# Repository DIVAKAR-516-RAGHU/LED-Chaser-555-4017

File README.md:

# 10-Stage Sequential LED Chaser (NE555 + CD4017)

A fully verified, 2-layer hardware design of a 10-stage sequential LED chaser circuit designed in **KiCad**. The board incorporates an analog astable pulse generator driving a CMOS Johnson decade counter with dedicated current-limited output stages and integrated ground copper fills.

---

## ⚡ Circuit Overview & Working Principle

The circuit is organized into three sequential functional stages:

1. **Clock Generator (NE555 Timer - Astable Mode):**
   * Configured as an astable multivibrator producing continuous square-wave clock pulses.
   * Timing is governed by external resistors $R_1$, $R_2$ and timing capacitor $C_1$:
     $$f \approx \frac{1.44}{(R_1 + 2R_2) \cdot C_1}$$
   * The output from pin 3 feeds directly into the clock input of the counter.

2. **Decade Counter & Sequencer (CD4017):**
   * High-speed CMOS 5-stage Johnson decade counter with 10 decoded active-high outputs ($Q_0$ through $Q_9$).
   * Advances one count on every positive clock edge received from the 555 timer.
   * Clock Inhibit (pin 13) and Master Reset (pin 15) are tied to ground for continuous, rollover cycling.

3. **Output Display (LED Array):**
   * 10 sequential 5 mm LEDs ($D_1$ to $D_{10}$), each paired with an independent 1 kΩ current-limiting resistor ($R_3$ to $R_{12}$) to maintain uniform brightness and prevent current crowding.

---

## 🛠️ Hardware & PCB Specifications

* **EDA Tool:** KiCad 8.0+
* **Layer Count:** 2-Layer (Top Copper / Bottom Copper)
* **Board Dimensions:** Defined via enclosed `Edge.Cuts` boundary
* **Substrate / Thickness:** FR-4 / 1.6 mm
* **Copper Weight:** 1 oz (35 µm)
* **Minimum Trace Width:** 0.25 mm (Signals) / 0.5 mm (Power rails)
* **Ground Strategy:** Solid ground fill on bottom copper (`B.Cu`) with thermal relief spokes on all grounded through-hole pads.
* **Decoupling / EMI Protection:** Dedicated 100 nF ceramic bypass capacitors located directly adjacent to $V_{CC}$ and $V_{DD}$ supply pins to suppress switching transients.
* **Design Verification:** Passed with **0 ERC (Electrical Rules Check)** and **0 DRC (Design Rules Check)** errors.

---

## 📋 Bill of Materials (BOM)

| Designator | Description / Value | Package / Footprint | Quantity |
| :--- | :--- | :--- | :--- |
| **U1** | NE555 Precision Timer IC | DIP-8 | 1 |
| **U2** | CD4017 Decade Counter/Divider IC | DIP-16 | 1 |
| **D1 – D10** | 5 mm Through-Hole LEDs | Radial LED 5 mm | 10 |
| **R1** | 10 kΩ Resistor, 1/4W | Axial Through-Hole | 1 |
| **R2** | 100 kΩ Resistor, 1/4W | Axial Through-Hole | 1 |
| **R3 – R12** | 1 kΩ Resistors, 1/4W | Axial Through-Hole | 10 |
| **C1** | 10 µF Electrolytic Capacitor | Radial 2.54 mm pitch | 1 |
| **C2** | 10 nF Ceramic Disc Capacitor | Radial 2.54 mm pitch | 1 |
| **C3, C4** | 100 nF Ceramic Bypass Capacitors | Radial 2.54 mm pitch | 2 |
| **J1** | 2-Pin Screw Terminal or 2.54 mm Header | 1x02 2.54 mm Pitch | 1 |

---

## 📁 Repository Structure

```text
├── Hardware/                         # Native KiCad design files
│   ├── LED Chaser (CD4017 + 555).kicad_pro
│   ├── LED Chaser (CD4017 + 555).kicad_sch
│   └── LED Chaser (CD4017 + 555).kicad_pcb
├── Production/                       # Manufacturing outputs
│   └── LED_Chaser_Fabrication.zip   # Gerber & Excellon drill files
├── assets/                           # Media & layout previews
│   ├── 3d_render.png
│   ├── pcb_layout.png
│   └── schematic_preview.png
├── .gitignore
└── README.md

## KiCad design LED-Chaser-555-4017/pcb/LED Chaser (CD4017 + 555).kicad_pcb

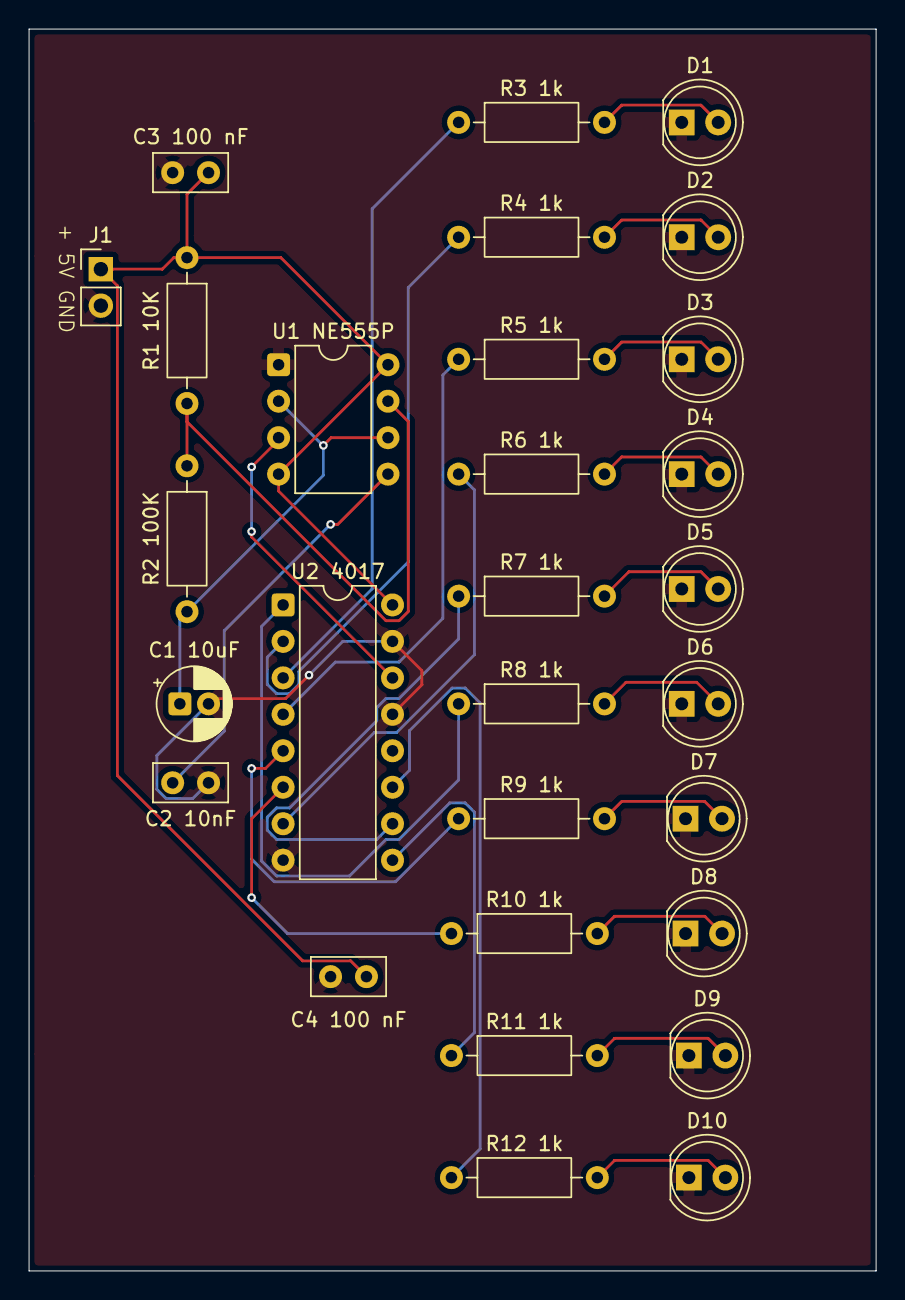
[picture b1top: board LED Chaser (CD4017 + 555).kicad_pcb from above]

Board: 2 copper layers, 59.0 x 86.5 mm, 29 parts (0 on the bottom side), 26 nets.

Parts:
C1 10uF: 10 uF; CP_Radial_D5.0mm_P2.00mm
C2 10nF: 10 nF; C_Disc_D5.0mm_W2.5mm_P2.50mm
C3 100 nF, C4 100 nF: 100 nF; C_Disc_D5.0mm_W2.5mm_P2.50mm
D1: D1 LED; LED_D5.0mm
D2: D2 LED; LED_D5.0mm
D3: D3 LED; LED_D5.0mm
D4: D4 LED; LED_D5.0mm
D5: D5 LED; LED_D5.0mm
D6: D6 LED; LED_D5.0mm
D7: D7 LED; LED_D5.0mm
D8: D8 LED; LED_D5.0mm
D9: D9 LED; LED_D5.0mm
D10: D10 LED; LED_D5.0mm
J1: Conn_01x02; PinHeader_1x02_P2.54mm_Vertical
R1 10K: 10k; R_Axial_DIN0207_L6.3mm_D2.5mm_P10.16mm_Horizontal
R2 100K: 100k; R_Axial_DIN0207_L6.3mm_D2.5mm_P10.16mm_Horizontal
R3 1k: R3 1k; R_Axial_DIN0207_L6.3mm_D2.5mm_P10.16mm_Horizontal
R4 1k: R4 1k; R_Axial_DIN0207_L6.3mm_D2.5mm_P10.16mm_Horizontal
R5 1k: R5 1k; R_Axial_DIN0207_L6.3mm_D2.5mm_P10.16mm_Horizontal
R6 1k: R6 1k; R_Axial_DIN0207_L6.3mm_D2.5mm_P10.16mm_Horizontal
R7 1k: R7 1k; R_Axial_DIN0207_L6.3mm_D2.5mm_P10.16mm_Horizontal
R8 1k: R8 1k; R_Axial_DIN0207_L6.3mm_D2.5mm_P10.16mm_Horizontal
R9 1k: R9 1k; R_Axial_DIN0207_L6.3mm_D2.5mm_P10.16mm_Horizontal
R10 1k: R10 1k; R_Axial_DIN0207_L6.3mm_D2.5mm_P10.16mm_Horizontal
R11 1k: R11 1k; R_Axial_DIN0207_L6.3mm_D2.5mm_P10.16mm_Horizontal
R12 1k: R12 1k; R_Axial_DIN0207_L6.3mm_D2.5mm_P10.16mm_Horizontal
U1 NE555P: NE555P; DIP-8_W7.62mm
U2 4017: 4017; DIP-16_W7.62mm

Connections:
+5V: C3 100 nF.2, C4 100 nF.2, J1.1, R1 10K.1, U1 NE555P.4 (~RST), U1 NE555P.8 (VCC), U2 4017.16 (VDD)
/CLOCK: U1 NE555P.3 (OUT), U2 4017.14 (CLK)
/Q0: R3 1k.1, U2 4017.3 (Q0)
/Q1: R4 1k.1, U2 4017.2 (Q1)
/Q2: R5 1k.1, U2 4017.4 (Q2)
/Q3: R6 1k.1, U2 4017.7 (Q3)
/Q4: R7 1k.1, U2 4017.10 (Q4)
/Q5: R8 1k.1, U2 4017.1 (Q5)
/Q6: R9 1k.1, U2 4017.5 (Q6)
/Q7: R10 1k.1, U2 4017.6 (Q7)
/Q8: R11 1k.1, U2 4017.9 (Q8)
/Q9: R12 1k.1, U2 4017.11 (Q9)
GND: C1 10uF.2, C2 10nF.1, C3 100 nF.1, C4 100 nF.1, D1.1 (K), D2.1 (K), D3.1 (K), D4.1 (K), D5.1 (K), D6.1 (K), D7.1 (K), D8.1 (K), D9.1 (K), D10.1 (K), J1.2, U1 NE555P.1 (GND), U2 4017.8 (VSS), U2 4017.13 (CKEN), U2 4017.15 (Reset)
unnamed: D1.2 (A), R3 1k.2
unnamed: D2.2 (A), R4 1k.2
unnamed: D3.2 (A), R5 1k.2
unnamed: D4.2 (A), R6 1k.2
unnamed: D5.2 (A), R7 1k.2
unnamed: D6.2 (A), R8 1k.2
unnamed: D7.2 (A), R9 1k.2
unnamed: D8.2 (A), R10 1k.2
unnamed: D9.2 (A), R11 1k.2
unnamed: D10.2 (A), R12 1k.2
unnamed: C2 10nF.2, U1 NE555P.5 (CONT)
unnamed: R1 10K.2, R2 100K.1, U1 NE555P.7 (DISCH)
unnamed: C1 10uF.1, R2 100K.2, U1 NE555P.2 (TRIG), U1 NE555P.6 (THRES)
